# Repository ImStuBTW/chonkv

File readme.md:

# ChonkV

The ChonkV is a 58 key choc keyboard based off Brickbot's excellent [chocV](https://github.com/brickbots/chocV) keyboard. It adds a number row, an additional outer column, and thumb keys in the style of the [Atreus keyboard](https://shop.keyboard.io/products/keyboardio-atreus).

This keyboard was designed largely as a way of learning the [Ergogen](https://docs.ergogen.xyz) keyboard layout generator software. I was pretty happy with my previous keyboard, the split Sofle Choc, but this new keyboard design allowed me to test a variety of concepts I'd been curious about experimenting with. The ChonkV has the same 58 key count as the Sofle Choc, but its unibody design makes it a bit more portable. This board also has true Choc spacing, and is my first time working with the Nice!Nano wireless microcontroller. While it's not a true ortholinear block, this is my first time dabbling with a board that drops the usual column stagger.

There's a few existing board designs that also may have checked these boxes. The keyboard community has putting out several interesting Reviung variants, and the Atreus also comes close to this design. I've always liked the look of the chocV however, and wanted to try my own spin at the design. This board's not nearly as smol, but I like it. It's chonky. It's a chonky chocV. The ChonkV.

## Features

* 58 key layout featuring number rows, outer columns, three modifiers on each side of the keyboard, raise and lower keys, and Atreus-style thumb keys for enter and space.
* Kailh Choc v1 Switches.
* Supports through-hole switch sholdering or Kailh Choc hotswap sockets.
* Choc switch spacing. (Has been bested with MBK keycaps.)
* Designed for the Nice!Nano wireless Microcontroller.
* Also supports the Nice!View display. (Nice!View requires an additional wire to be run from the display's CS pin to one of the Nice!Nano's extra internal pins.)
* JST battery connector.
* RST pushbutton.
* Physical power switch.
* Includes designs for a Horizon/ChocV style PCB backplate as well as a more traditional 3D printed case.

## Ergogen Files

**Just an FYI for those looking to use this as a reference to learn Ergogen. This library leverages Ergogen 3, and several custom footprints that can be found in [my fork repo](https://github.com/ImStuBTW/ergogen). Ergogen 4 made several breaking changes to the syntax in December of 2022, so make sure you check which version you're using if you reference these config files for your own project.**

### chonkv.yaml

This is the main file for the ChonkV PCB. It is designed with choc spacing, and has a 3mm padding around the edge of the keyboard. The microcontroller is mounted in the middle of the keyboard, along with a reset button and JST header. There's a small bit of PCB art by the thumbs. Running this config file through Ergogen will generate the ChonkV PCB, the board's outlines, as well as some 3D printing .stl case files.

### chonkv_case.yaml

This file was used in the creation of a fairly straightforward keycoard case. It uses 2M standoffs to support the PCB, and gives it a small border outside of the premiter. This config file is seperate from the main chonkv.yaml due to Ergogen limitations on "glue" outlines. It creates an outline that is a few mm larger than the main PCB file.

Unfortunately, since this case design is split between chonkv.yaml and chonkv_case.yaml, Ergogen can't put together all the finished pieces for us. You'll need to import them into some CAD software like TinkerCAD to get the final design output. Or you can just download it from this repo of course.

One thing you may notice is that the whole for the standoffs goes all the way through the 3D model. This is supposed to be a low profile case, so the metal standoffs are designed to sit flush with the bottom of the case.

### chonkv_backplate.yaml

This was a largely failed experiment. The original chocV keyboard included designs for a second inert PCB that would screw onto the bottom of the main PCB to give the board some extra stability and shiled the exposed metal legs of the soldered components. I was always fond of this design, but it was limited to through-hole designs. I came up with some choc hotswap footprints with a cutout for the hotswap sockets, but the resulting cuts were large, complex, and covered most of the board. I haven't tried submitting them to a PCB fab, but I assume they'd try to include an extra charge this backplate. On top of that, the hotswap sockets stick out about 2mm on the bottom of a board, and most PCBs are about 1.8mm thick. I'd like to itterate on this concept some day (or just commit to a through-hole design), but I'm tabling this concept for now.

The backplate design wasn't a complete waste however. I was able to include the backplate design in the 3D printed case I created with chonkv_case.yaml, so the resulting 3D printed case is now a bit more sturdy and less echoy.

## Finished Files

If you don't want to go through the build process yourself, you can always download the files found in the "outputs" folder. It has a zipped Gerbers file, the complex case .stl, and a simplified case .stl. The .stl files have been split into left and right halves in case you have a 3D printer with a smaller print volume.

## Build of Materials

| Part                                      | Amount               | Approx. Price (Total) | Link |
| ----------------------------------------- | -------------------- | --------------------- | ---- |
| ChonkV PCB Fab Via JLCPCB (With Shipping) | 1                    | $28.00 USD (2 Week Shipping) | https://jlcpcb.com |
| Nice!Nano Microcontroller                 | 1                    | $22.00 USD            | https://42keebs.eu/shop/parts/controllers/nice-nano-v2-wireless-controller/ |
| Nice!View Sharp Memory Display            | 1                    | $19.00 USD            | https://42keebs.eu/shop/parts/niceview-power-efficient-lcd-display/ |
| Kailh Choc v2 Switches                    | 6 (58 Keys Total)    | $30.00 USD            | https://42keebs.eu/shop/switches/choc/kailh-choc-low-profile-switches/ |
| 1N4148 Diodes (SMD)                       | 6 (58 Diodes Total)  | $2.00 USD             | https://42keebs.eu/shop/parts/components/1n4148-diodes-through-hole-smd/ |
| Kailh Choc Hotswap Sockets                | 6 (58 Sockets Total) | $10.00 USD            | https://42keebs.eu/shop/parts/kailh-choc-hot-swap-sockets/ |
| Power Switch                              | 1                    | $0.50 USD             | https://42keebs.eu/shop/parts/components/power-switch/ |
| Reset Switch (6x3mm, THD)                 | 1                    | $0.50 USD             | https://42keebs.eu/shop/parts/components/reset-switch/ |
| Mill Max Sockets & Pins                   | 1                    | $7.50 USD             | https://42keebs.eu/shop/parts/components/mill-max-315-sockets-3320-pins-for-pro-micro/ |
| Medium Profile Controller Socket          | 1                    | $0.50 USD             | https://42keebs.eu/shop/parts/components/microcontroller-socket-medium-profile/ |
| Additional Mill Max Pins (For Nice!View)  | 1                    | $3.50 USD             | https://42keebs.eu/shop/parts/components/mill-max-315-sockets-3320-pins-for-pro-micro/ |
| JST Header (2P)                           | 1                    | $4.00 USD             | https://www.aliexpress.us/item/2251832866999242.html |
| Choc v1 Keycaps                           | 1                    | $75.00 USD            | https://mkultra.click/mbk-legend-keycaps/ |
| 100 mAh LiPo Battery (Left Pos.) LP401230 | 1                    | $12.00 USD            | https://www.amazon.com/dp/B0137KTPP0 |

You may be able to get some of the parts cheaper (or at least in bulk) on Aliexpress. 42Keebs has good prices on Nice!Nano and Nice!View microcontrollers, and you can pick up a lot of other parts while you're at it. Batteries you'll need to get domestically, and keycap avalability is subject to change. You should be able to build this keyboard for about $225 USD, give or take some shipping costs.

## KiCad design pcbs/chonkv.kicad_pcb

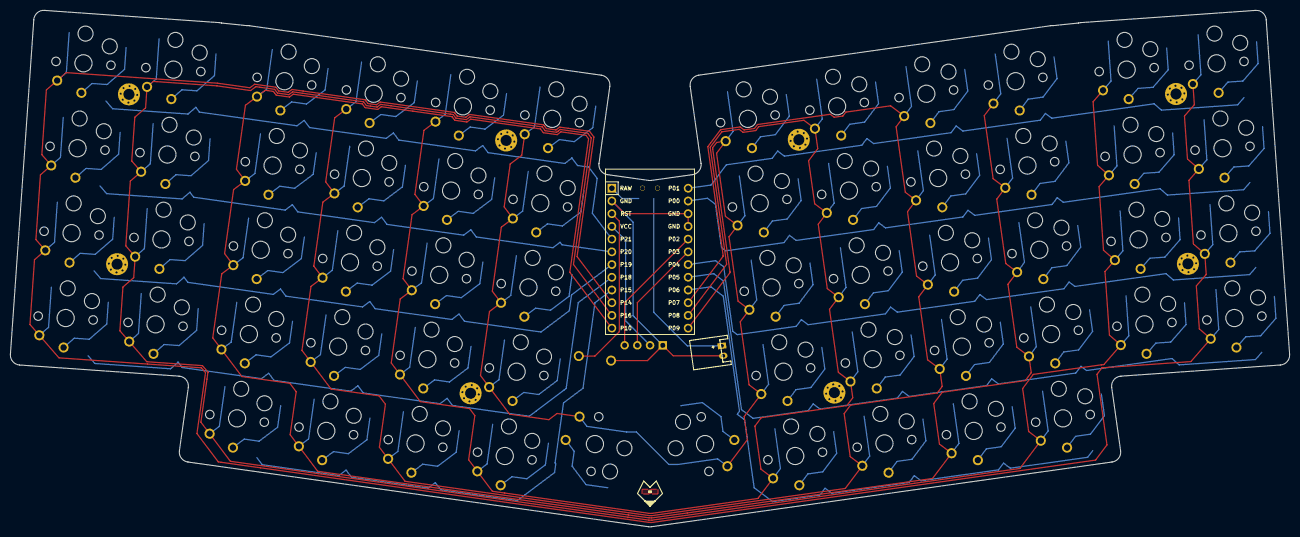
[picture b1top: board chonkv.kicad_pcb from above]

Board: 2 copper layers, 255.5 x 103.2 mm, 129 parts (0 on the bottom side), 81 nets.

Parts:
B1: ResetSW
D1, D2, D3, D4, D5, D6, D7, D8, D9, D10, D11, D12, D13, D14, D15, D16, D17, D18, D19, D20, D21, D22, D23, D24, D25, D26, D27, D28, D29, D30, D31, D32, D33, D34, D35, D36, D37, D38, D39, D40, D41, D42, D43, D44, D45, D46, D47, D48, D49, D50, D51, D52, D53, D54, D55, D56, D57, D58: ComboDiode
HOLE1, HOLE2, HOLE3, HOLE4, HOLE5, HOLE6, HOLE7, HOLE8: MountingHole_2.2mm_M2_Pad_Via
JST1: JST_PH_S2B-PH-K_02x2.00mm_Angled
MCU1: ProMicro
OLED1: OLED; OLED_headers
S1, S2, S3, S4, S5, S6, S7, S8, S9, S10, S11, S12, S13, S14, S15, S16, S17, S18, S19, S20, S21, S22, S23, S24, S25, S26, S27, S28, S29, S30, S31, S32, S33, S34, S35, S36, S37, S38, S39, S40, S41, S42, S43, S44, S45, S46, S47, S48, S49, S50, S51, S52, S53, S54, S55, S56, S57, S58: PG1350
T1: SPDT_C128955

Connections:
BAT_POS: JST1.1, T1.2
GND: B1.2, JST1.2, MCU1.2, MCU1.15, MCU1.16, OLED1.1
P0: D32.1, D36.1, D41.1, D46.1, D51.1, D56.1, MCU1.14
P1: D33.1, D37.1, D42.1, D47.1, D52.1, D57.1, MCU1.13
P2: MCU1.17, OLED1.4
P3: MCU1.18, OLED1.3
P4: D31.1, D35.1, D40.1, D45.1, D50.1, D55.1, MCU1.19
P5: D30.1, D34.1, D39.1, D44.1, D49.1, D54.1, MCU1.20
P6: D38.1, D43.1, D48.1, D53.1, D58.1, MCU1.21
P7: MCU1.22, S15.1, S16.1, S17.1, S18.1, S19.1, S44.1, S45.1, S46.1, S47.1, S48.1
P8: MCU1.23, S20.1, S21.1, S22.1, S23.1, S24.1, S49.1, S50.1, S51.1, S52.1, S53.1
P9: MCU1.24, S25.1, S26.1, S27.1, S28.1, S29.1, S54.1, S55.1, S56.1, S57.1, S58.1
P10: MCU1.12, S10.1, S11.1, S12.1, S13.1, S14.1, S39.1, S40.1, S41.1, S42.1, S43.1
P14: MCU1.10, S1.1, S2.1, S3.1, S4.1, S30.1, S31.1, S32.1, S33.1
P15: D9.1, D14.1, D19.1, D24.1, D29.1, MCU1.9
P16: MCU1.11, S5.1, S6.1, S7.1, S8.1, S9.1, S34.1, S35.1, S36.1, S37.1, S38.1
P18: D1.1, D5.1, D10.1, D15.1, D20.1, D25.1, MCU1.8
P19: D2.1, D6.1, D11.1, D16.1, D21.1, D26.1, MCU1.7
P20: D3.1, D7.1, D12.1, D17.1, D22.1, D27.1, MCU1.6
P21: D4.1, D8.1, D13.1, D18.1, D23.1, D28.1, MCU1.5
RAW: MCU1.1, T1.1
RST: B1.1, MCU1.3
VCC: MCU1.4, OLED1.2
index_bottom: D20.2, S20.2
index_home: D21.2, S21.2
index_mod: D19.2, S19.2
index_num: D23.2, S23.2
index_top: D22.2, S22.2
inner_bottom: D25.2, S25.2
inner_home: D26.2, S26.2
inner_mod: D24.2, S24.2
inner_num: D28.2, S28.2
inner_top: D27.2, S27.2
middle_bottom: D15.2, S15.2
middle_home: D16.2, S16.2
middle_mod: D14.2, S14.2
middle_num: D18.2, S18.2
middle_top: D17.2, S17.2
mirror_index_bottom: D49.2, S49.2
mirror_index_home: D50.2, S50.2
mirror_index_mod: D48.2, S48.2
mirror_index_num: D52.2, S52.2
mirror_index_top: D51.2, S51.2
mirror_inner_bottom: D54.2, S54.2
mirror_inner_home: D55.2, S55.2
mirror_inner_mod: D53.2, S53.2
mirror_inner_num: D57.2, S57.2
mirror_inner_top: D56.2, S56.2
mirror_middle_bottom: D44.2, S44.2
mirror_middle_home: D45.2, S45.2
mirror_middle_mod: D43.2, S43.2
mirror_middle_num: D47.2, S47.2
mirror_middle_top: D46.2, S46.2
mirror_outer_bottom: D30.2, S30.2
mirror_outer_home: D31.2, S31.2
mirror_outer_num: D33.2, S33.2
mirror_outer_top: D32.2, S32.2
mirror_pinky_bottom: D34.2, S34.2
mirror_pinky_home: D35.2, S35.2
mirror_pinky_num: D37.2, S37.2
mirror_pinky_top: D36.2, S36.2
mirror_ring_bottom: D39.2, S39.2
mirror_ring_home: D40.2, S40.2
mirror_ring_mod: D38.2, S38.2
mirror_ring_num: D42.2, S42.2
mirror_ring_top: D41.2, S41.2
mirror_thumb_mod: D58.2, S58.2
outer_bottom: D1.2, S1.2
outer_home: D2.2, S2.2
outer_num: D4.2, S4.2
outer_top: D3.2, S3.2
pinky_bottom: D5.2, S5.2
pinky_home: D6.2, S6.2
pinky_num: D8.2, S8.2
pinky_top: D7.2, S7.2
ring_bottom: D10.2, S10.2
ring_home: D11.2, S11.2
ring_mod: D9.2, S9.2
ring_num: D13.2, S13.2
ring_top: D12.2, S12.2
thumb_mod: D29.2, S29.2

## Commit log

2022-12-28 Initial Design. Readme TBD.
2022-12-28 Added MIT license.
2022-12-29 Added ZMK config files.
2022-12-29 Added PCB render image.
2022-12-29 Image fix.
2022-12-29 Updated ReadMe.
2023-02-19 Case Adjustments
2023-02-19 Fixed a typo.
2024-09-10 Updated ZMK Config
